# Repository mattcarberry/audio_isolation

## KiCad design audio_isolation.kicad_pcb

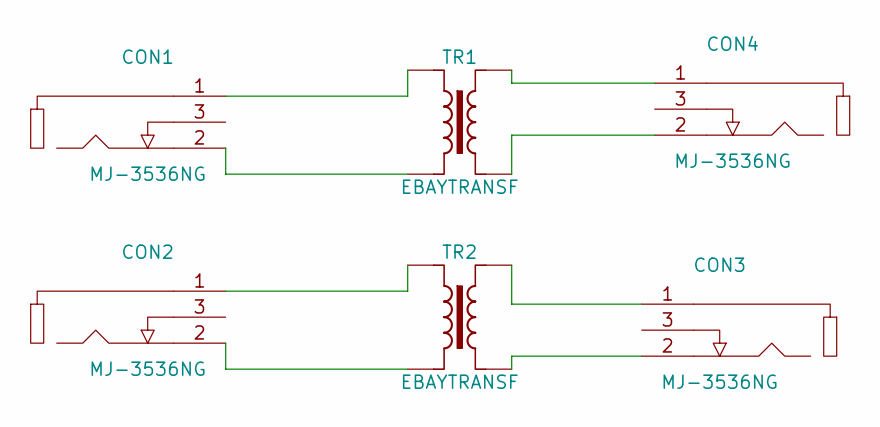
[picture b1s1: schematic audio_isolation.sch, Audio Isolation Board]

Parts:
CON1, CON2, CON3, CON4: MJ-3536NG
TR1, TR2: EBAYTRANSF; ebaytransf

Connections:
unnamed: CON1.1, TR1.1
unnamed: CON1.2, TR1.2
unnamed: CON2.1, TR2.1
unnamed: CON2.2, TR2.2
unnamed: CON3.1, TR2.4
unnamed: CON3.2, TR2.3
unnamed: CON4.1, TR1.4
unnamed: CON4.2, TR1.3

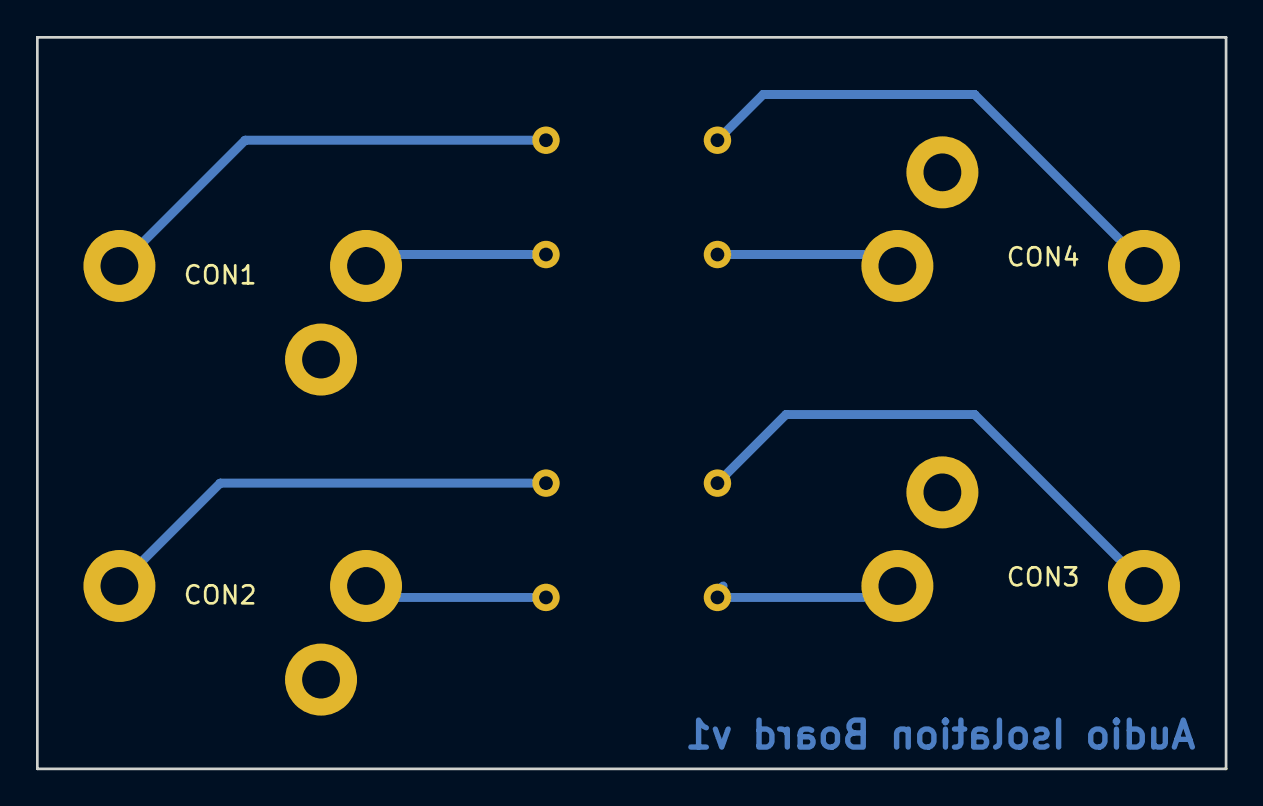
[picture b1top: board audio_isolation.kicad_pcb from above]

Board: 2 copper layers, 66.0 x 40.6 mm, 6 parts (0 on the bottom side), 8 nets.

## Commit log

2016-09-21 Initial commit of the libaries, footprint, schematic, and pcb layout for an Audio Isolator using a transformer.
